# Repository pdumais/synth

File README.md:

# Modular Synthesizer

# Design
- 5V system, but requires +12,-12 rails for modules using opamps
- uses computer PSU
- 2 signal paths:
    1) The audio signal. -5 - +5V. 
    2) Control Voltages. They work on unipolar 5V.

# Current modules
- [dual VCO and quad LFO. Square only](modules/osc)
- [LFO shaper: to convert square to trianble/sine or anything in between](modules/waveshaper)
- [Sequencer](modules/sequencer)
- [Clock](modules/clock)
- [Clock Divider](modules/divider)
- [Voltage Controlled Resistors](modules/digipot)
- [Midi2CV](modules/midi2cv)
- [Noise Generator](modules/noise)
- [4 Channel VCA](modules/vca)
- [4 stage VCF](modules/vcf)

# Known issues
- Power filtering
    The oscilloscope shows that the -5 and +5 rails oscillate at an amplitude of 0.4v. The wave has a period of 500ns.
    That's 2mhz. 
    For the CV path, this gets filtered out by the sampling rate of the ADC, so no need to do anything about it. When CV
    is used with analog, it wouldn't be audible anyway.

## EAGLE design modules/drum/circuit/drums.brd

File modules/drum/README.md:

Bass drum demo: https://www.youtube.com/watch?v=A4alrGFjpv0

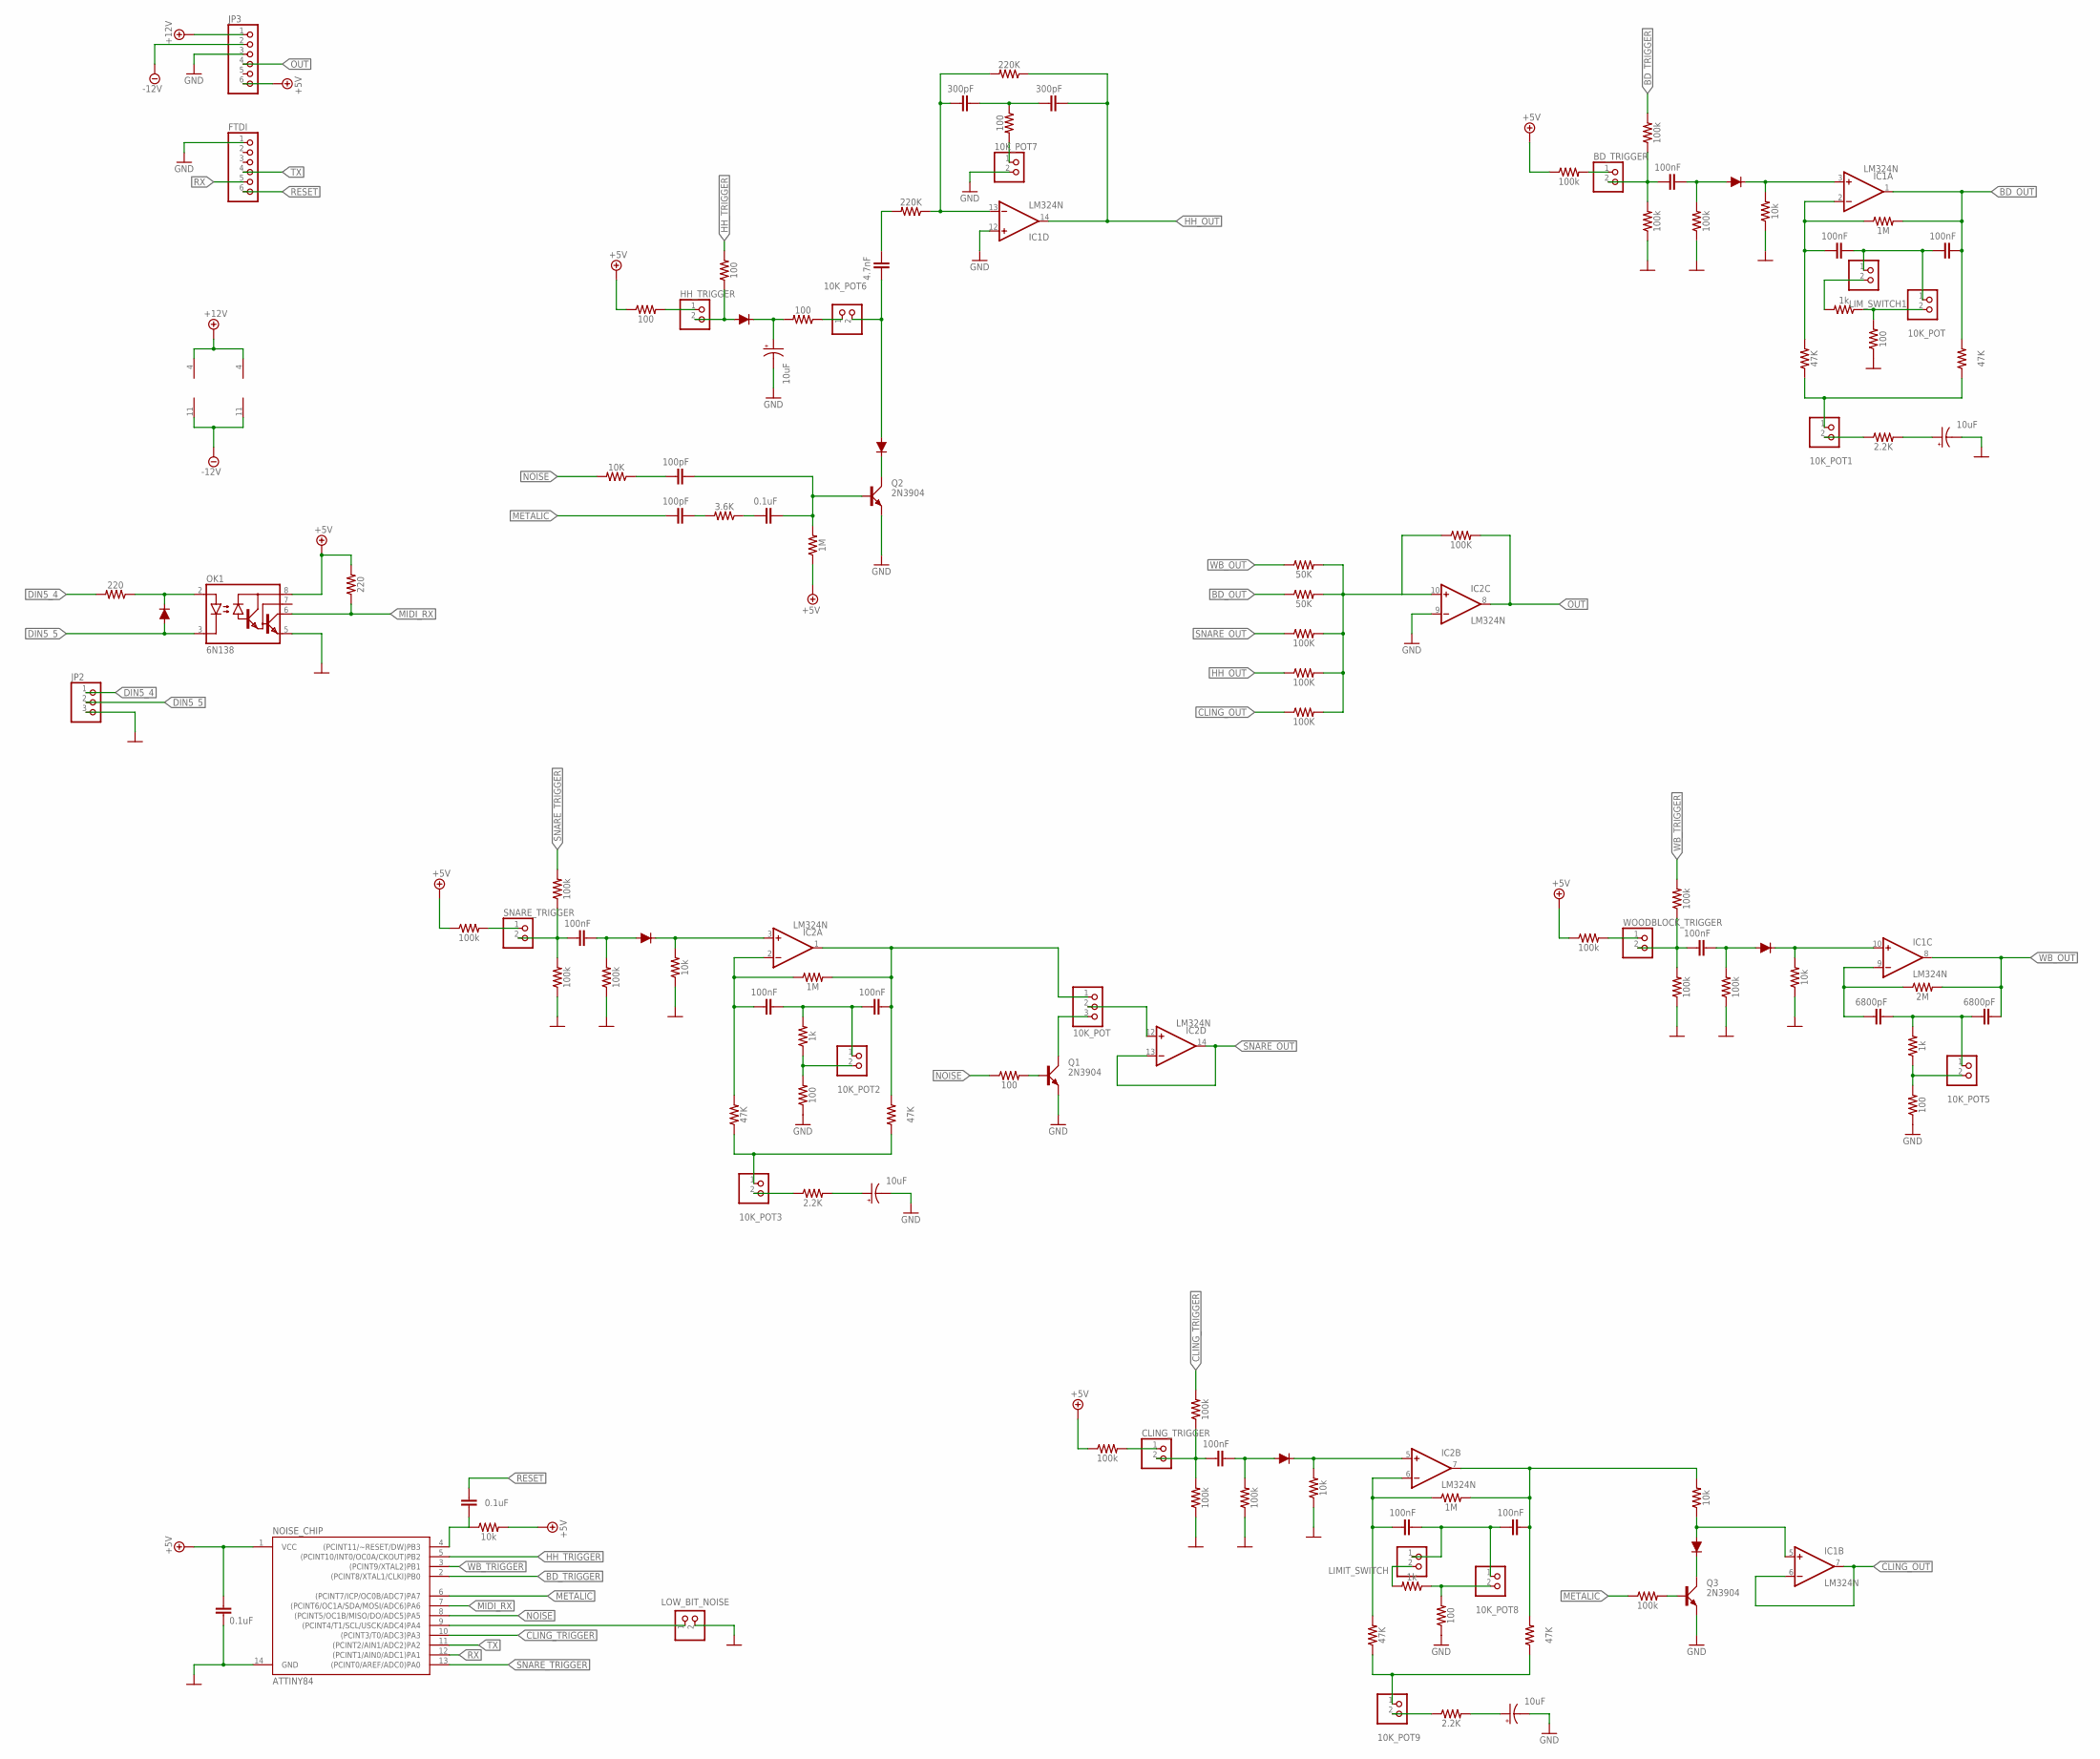
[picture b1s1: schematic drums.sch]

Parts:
1M: 1M; AXIAL-0.3
1M1, 1M2: 220; AXIAL-0.3
10K_POT, 10K_POT1, 10K_POT2, 10K_POT3, 10K_POT5, 10K_POT6, 10K_POT7, 10K_POT8, 10K_POT9: PINHD-1X2; 1X02
10K_POT4: 10K_POT; 1X03
BD_TRIGGER: PINHD-1X2; 1X02
C1, C4, C12: 0.1uF; C5B3
C2, C3, C6, C7, C18, C19, C20, C21, C22, C24: 100nF; C5B3
C5, C8, C11, C23: 10uF; TT5D11
C9, C10: 6800pF; C5B3
C13, C14: 100pF; C5B3
C15: 4.7nF; C5B3
C16, C17: 300pF; C5B3
CLING_TRIGGER: PINHD-1X2; 1X02
D1, D2, D3, D4, D5, D6, D7, D8: 1A/50V/1.1V; DIODE-1N4001-KIT
FTDI: PINHD-1X6; 1X06
HH_TRIGGER: PINHD-1X2; 1X02
IC1, IC2: LM324N; DIL14
JP2: PINHD-1X3; 1X03
JP3: PINHD-1X6; 1X06
LIMIT_SWITCH: PINHD-1X2; 1X02
LIM_SWITCH1: PINHD-1X2; 1X02
LOW_BIT_NOISE: PINHD-1X2; 1X02
NOISE_CHIP: ATTINY84; DIP14
OK1: 6N138; DIL08
Q1, Q2, Q3: 2N3904; TO92D
R1, R12, R19, R20, R23, R38, R39, R41, R42, R43, R44, R45, R52, R54, R55, R56, R57: 100k; AXIAL-0.3
R2, R22, R25, R40, R53, R59: 10k; AXIAL-0.3
R3, R13, R46: 1M; AXIAL-0.3
R4, R5, R14, R15, R47, R48: 47K; AXIAL-0.3
R6, R16, R27, R49: 1k; AXIAL-0.3
R7, R11, R17, R21, R26, R28, R29, R36, R50: 100; AXIAL-0.3
R8, R18, R51: 2.2K; AXIAL-0.3
R9, R31: 50K; AXIAL-0.3
R10, R30, R37, R58: 100K; AXIAL-0.3
R24: 2M; AXIAL-0.3
R32: 3.6K; AXIAL-0.3
R33: 10K; AXIAL-0.3
R34, R35: 220K; AXIAL-0.3
SNARE_TRIGGER: PINHD-1X2; 1X02
WOODBLOCK_TRIGGER: PINHD-1X2; 1X02

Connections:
10K_POT1: 10K_POT1.1, R4.P$1 (1), R5.P$1 (1)
10K_POT2: 10K_POT3.1, R14.P$1 (1), R15.P$1 (1)
10K_POT3: 10K_POT9.1, R47.P$1 (1), R48.P$1 (1)
+5V: 1M.P$1 (1), 1M1.P$2 (2), C1.1, JP3.6, NOISE_CHIP.1 (VCC), OK1.8 (VCC), R23.P$1 (1), R25.P$2 (2), R29.P$1 (1), R38.P$1 (1), R41.P$1 (1), R54.P$1 (1)
+12V: IC1.4 (V+), IC2.4 (V+), JP3.1
-12V: IC1.11 (V-), IC2.11 (V-), JP3.2
BD_OUT: 10K_POT4.1, C3.2, C7.2, IC1.1 (OUT), IC2.1 (OUT), R3.P$2 (2), R5.P$2 (2), R13.P$2 (2), R15.P$2 (2), R31.P$1 (1)
BD_OUT1: C22.2, IC2.7 (OUT), R46.P$2 (2), R48.P$2 (2), R59.P$2 (2)
BD_TRIGGER: NOISE_CHIP.2 ((PCINT8/XTAL1/CLKI)PB0), R12.P$2 (2)
CLING_OUT: IC1.6 (-IN), IC1.7 (OUT), R58.P$1 (1)
CLING_TRIGGER: NOISE_CHIP.10 ((PCINT3/T0/ADC3)PA3), R57.P$2 (2)
DIN5_4: 1M2.P$2 (2), JP2.1
DIN5_5: D2.A, JP2.2, OK1.3 (C)
GND: 10K_POT7.2, C1.2, C5.-, C8.-, C11.-, C23.-, FTDI.1, IC1.12 (+IN), IC2.9 (-IN), JP2.3, JP3.3, LOW_BIT_NOISE.2, NOISE_CHIP.14 (GND), OK1.5 (GND), Q1.E, Q2.E, Q3.E, R1.P$1 (1), R2.P$1 (1), R7.P$1 (1), R17.P$1 (1), R22.P$1 (1), R28.P$1 (1), R39.P$1 (1), R40.P$1 (1), R42.P$1 (1), R43.P$1 (1), R44.P$1 (1), R45.P$1 (1), R50.P$1 (1), R53.P$1 (1), R55.P$1 (1), R56.P$1 (1)
HH_OUT: C17.2, IC1.14 (OUT), R35.P$1 (1), R37.P$1 (1)
HH_TRIGGER: NOISE_CHIP.5 ((PCINT10/INT0/OC0A/CKOUT)PB2), R11.P$2 (2)
METALIC: C14.1, NOISE_CHIP.6 ((PCINT7/ICP/OC0B/ADC7)PA7), R52.P$1 (1)
MIDI_RX: 1M1.P$1 (1), NOISE_CHIP.7 ((PCINT6/OC1A/SDA/MOSI/ADC6)PA6), OK1.6 (VO)
unnamed: 10K_POT8.1, C21.2, C22.1, LIMIT_SWITCH.1
unnamed: BD_TRIGGER.2, C18.1, R12.P$1 (1), R39.P$2 (2)
unnamed: D1.C, IC1.3 (+IN), R2.P$2 (2)
unnamed: C18.2, D1.A, R1.P$2 (2)
unnamed: BD_TRIGGER.1, R38.P$2 (2)
unnamed: 10K_POT.1, C2.2, C3.1, LIM_SWITCH1.1
unnamed: C2.1, IC1.2 (-IN), R3.P$1 (1), R4.P$2 (2)
unnamed: C21.1, IC2.6 (-IN), R46.P$1 (1), R47.P$2 (2)
unnamed: 10K_POT.2, R6.P$1 (1), R7.P$2 (2)
unnamed: 10K_POT1.2, R8.P$1 (1)
unnamed: C5.+, R8.P$2 (2)
unnamed: 1M2.P$1 (1), D2.C, OK1.2 (A)
unnamed: 10K_POT8.2, R49.P$1 (1), R50.P$2 (2)
unnamed: 10K_POT9.2, R51.P$1 (1)
unnamed: C19.1, R19.P$1 (1), R42.P$2 (2), WOODBLOCK_TRIGGER.2
unnamed: 10K_POT2.1, C6.2, C7.1, R16.P$2 (2)
unnamed: C6.1, IC2.2 (-IN), R13.P$1 (1), R14.P$2 (2)
unnamed: 10K_POT2.2, R16.P$1 (1), R17.P$2 (2)
unnamed: 10K_POT3.2, R18.P$1 (1)
unnamed: C8.+, R18.P$2 (2)
unnamed: C23.+, R51.P$2 (2)
unnamed: Q1.B, R21.P$2 (2)
unnamed: 10K_POT4.3, Q1.C
unnamed: 10K_POT4.2, IC2.12 (+IN)
unnamed: C20.1, R20.P$1 (1), R44.P$2 (2), SNARE_TRIGGER.2
unnamed: D3.C, IC2.3 (+IN), R22.P$2 (2)
unnamed: R23.P$2 (2), SNARE_TRIGGER.1
unnamed: D6.C, IC1.10 (+IN), R40.P$2 (2)
unnamed: 10K_POT5.1, C9.2, C10.1, R27.P$2 (2)
unnamed: C9.1, IC1.9 (-IN), R24.P$1 (1)
unnamed: 10K_POT5.2, R27.P$1 (1), R28.P$2 (2)
unnamed: D4.A, HH_TRIGGER.2, R11.P$1 (1)
unnamed: C11.+, D4.C, R26.P$2 (2)
unnamed: IC2.10 (+IN), R9.P$2 (2), R10.P$2 (2), R30.P$1 (1), R31.P$2 (2), R37.P$2 (2), R58.P$2 (2)
unnamed: 10K_POT6.1, R26.P$1 (1)
unnamed: 10K_POT6.2, C15.1, D5.A
unnamed: C4.2, NOISE_CHIP.4 ((PCINT11/~RESET/DW)PB3), R25.P$1 (1)
unnamed: D5.C, Q2.C
unnamed: C12.1, R32.P$1 (1)
unnamed: 1M.P$2 (2), C12.2, C13.2, Q2.B
unnamed: HH_TRIGGER.1, R29.P$2 (2)
unnamed: C13.1, R33.P$1 (1)
unnamed: C15.2, R34.P$2 (2)
unnamed: C14.2, R32.P$2 (2)
unnamed: 10K_POT7.1, R36.P$2 (2)
unnamed: C16.2, C17.1, R36.P$1 (1)
unnamed: R41.P$2 (2), WOODBLOCK_TRIGGER.1
unnamed: C16.1, IC1.13 (-IN), R34.P$1 (1), R35.P$2 (2)
unnamed: C19.2, D6.A, R43.P$2 (2)
unnamed: C20.2, D3.A, R45.P$2 (2)
unnamed: Q3.B, R52.P$2 (2)
unnamed: D8.C, Q3.C
unnamed: D8.A, IC1.5 (+IN), R59.P$1 (1)
unnamed: C24.1, CLING_TRIGGER.2, R55.P$2 (2), R57.P$1 (1)
unnamed: D7.C, IC2.5 (+IN), R53.P$2 (2)
unnamed: CLING_TRIGGER.1, R54.P$2 (2)
unnamed: C24.2, D7.A, R56.P$2 (2)
unnamed: LIM_SWITCH1.2, R6.P$2 (2)
unnamed: LIMIT_SWITCH.2, R49.P$2 (2)
unnamed: LOW_BIT_NOISE.1, NOISE_CHIP.9 ((PCINT4/T1/SCL/USCK/ADC4)PA4)
NOISE: NOISE_CHIP.8 ((PCINT5/OC1B/MISO/DO/ADC5)PA5), R21.P$1 (1), R33.P$2 (2)
OUT: IC2.8 (OUT), JP3.4, R30.P$2 (2)
RESET: C4.1, FTDI.6
RX: FTDI.5, NOISE_CHIP.12 ((PCINT1/AIN0/ADC1)PA1)
SNARE_OUT: IC2.13 (-IN), IC2.14 (OUT), R10.P$1 (1)
SNARE_TRIGGER: NOISE_CHIP.13 ((PCINT0/AREF/ADC0)PA0), R20.P$2 (2)
TX: FTDI.4, NOISE_CHIP.11 ((PCINT2/AIN1/ADC2)PA2)
WB_OUT: C10.2, IC1.8 (OUT), R9.P$1 (1), R24.P$2 (2)
WB_TRIGGER: NOISE_CHIP.3 ((PCINT9/XTAL2)PB1), R19.P$2 (2)

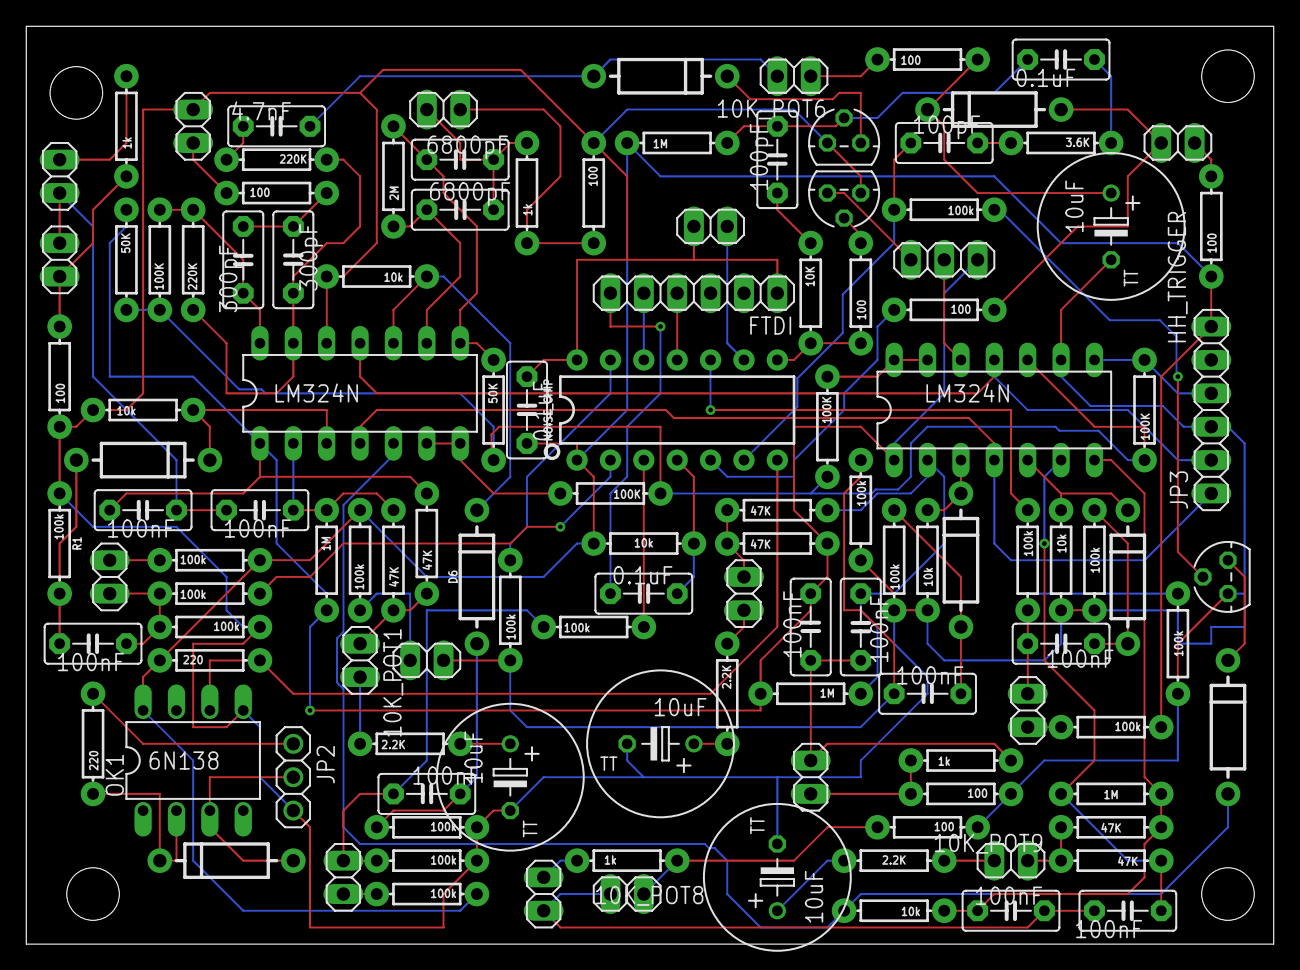
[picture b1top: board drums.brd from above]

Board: 2 copper layers, 94.9 x 69.8 mm, 122 parts (0 on the bottom side), 87 nets.

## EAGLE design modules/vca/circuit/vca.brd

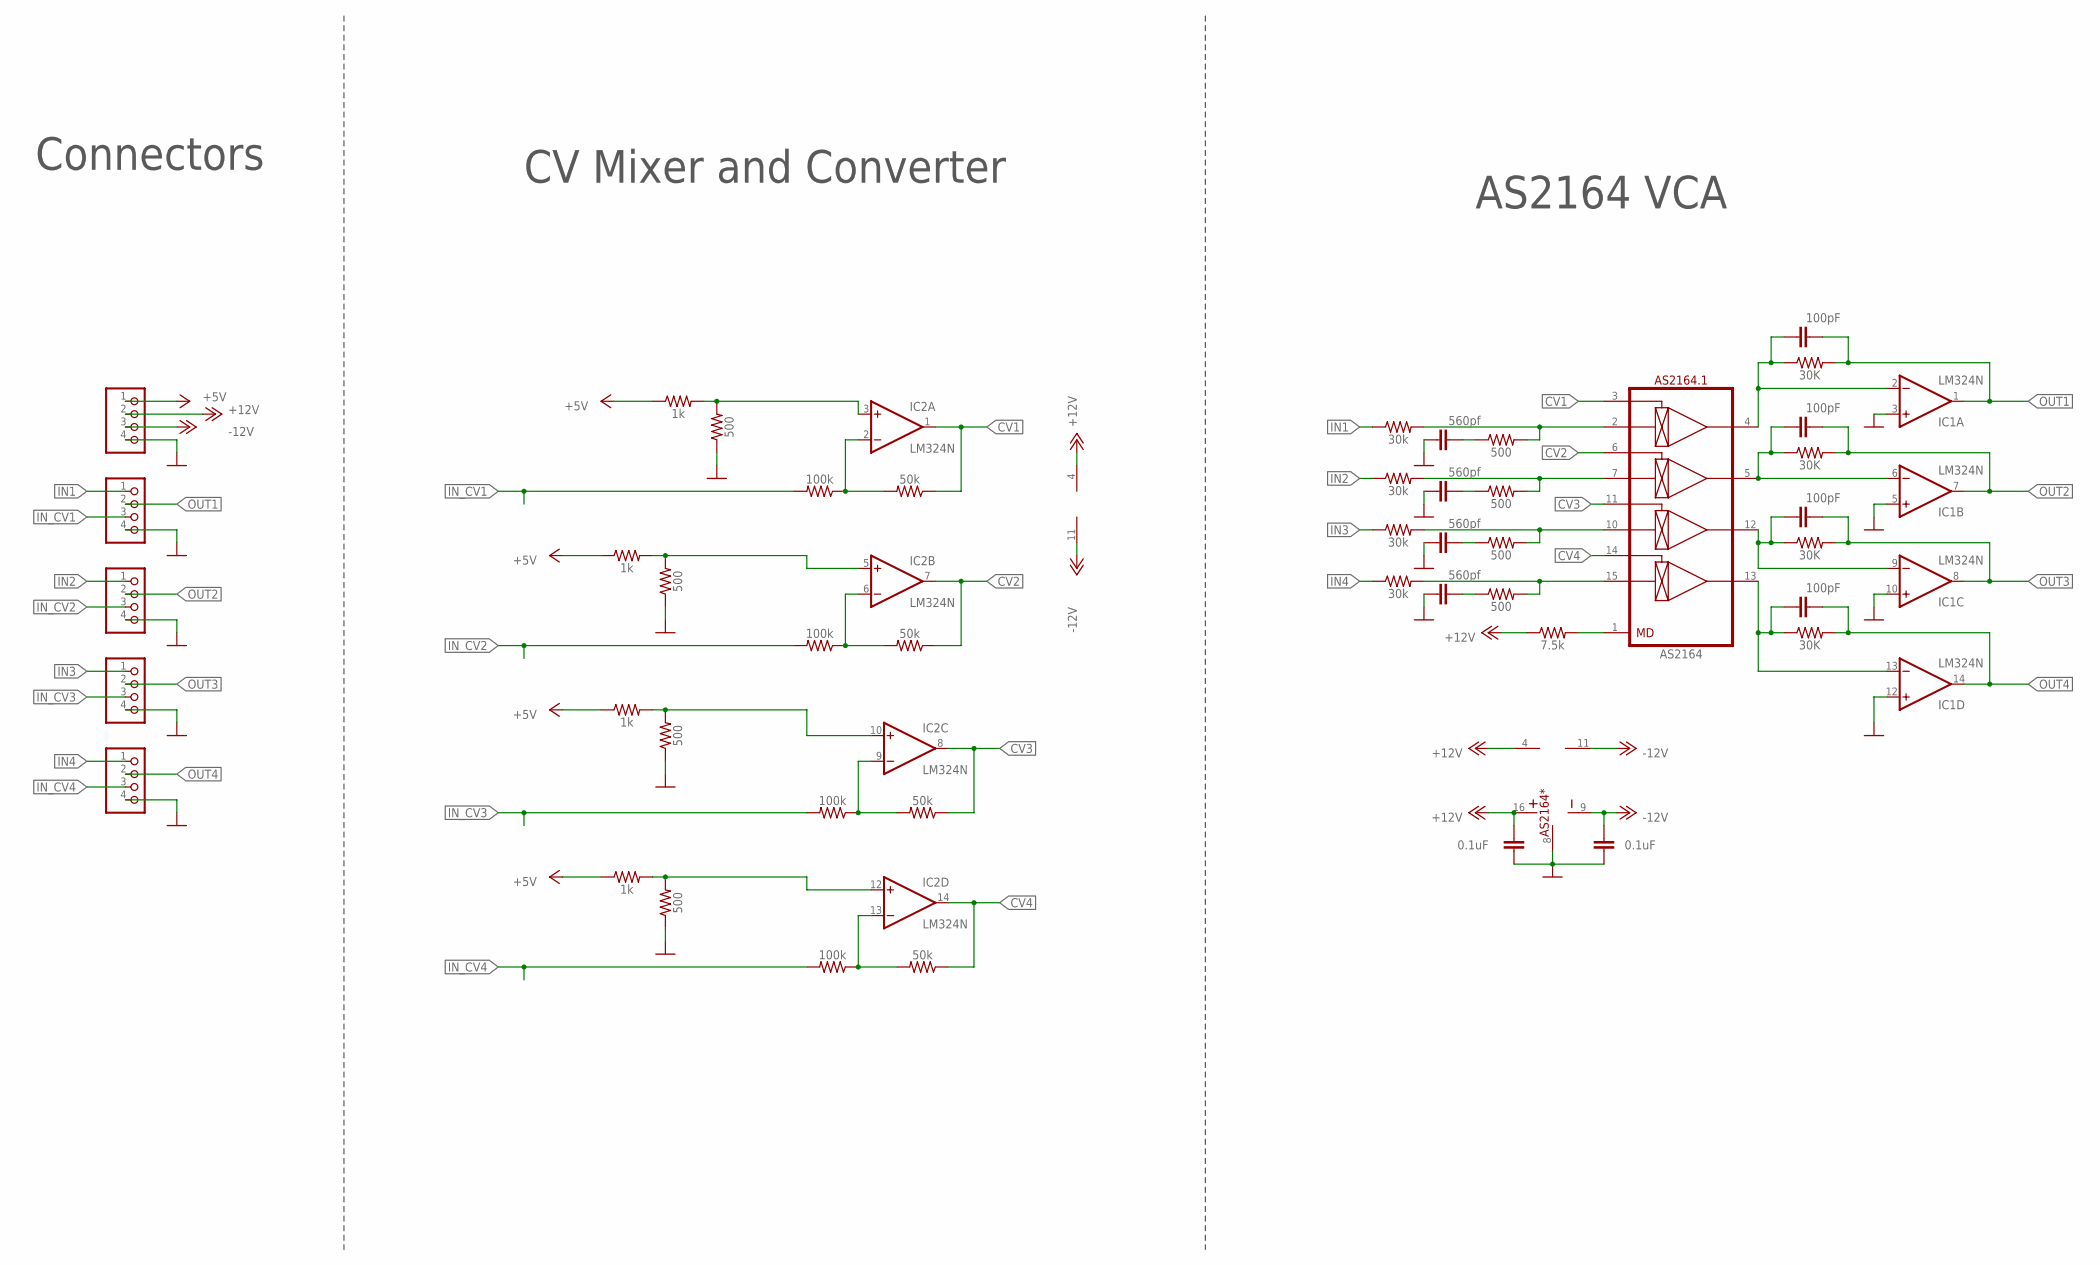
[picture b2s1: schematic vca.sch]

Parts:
AS2164: AS2164; DIP-16
C1, C2, C3, C4: 560pf; CAP-PTH-SMALL-KIT
C5, C6: 0.1uF; CAP-PTH-SMALL-KIT
C7, C8, C9, C10: 100pF; CAP-PTH-SMALL-KIT
IC1, IC2: LM324N; DIL14
JP1, JP5, JP6, JP7, JP8: PINHD-1X4; 1X04
R1, R2, R3, R5: 30k; AXIAL-0.3
R4, R6, R7, R8, R9, R14, R18, R22: 500; AXIAL-0.3
R10, R13, R17, R21: 1k; AXIAL-0.3
R11, R15, R19, R23: 100k; AXIAL-0.3
R12, R16, R20, R24: 50k; AXIAL-0.3
R25: 7.5k; AXIAL-0.3
R26, R27, R28, R29: 30K; AXIAL-0.3

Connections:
+5V: JP6.1, R10.P$1 (1), R13.P$1 (1), R17.P$1 (1), R21.P$1 (1)
+12V: AS2164.16 (V+), C5.2, IC1.4 (V+), IC2.4 (V+), JP6.2, R25.P$1 (1)
-12V: AS2164.9 (V-), C6.2, IC1.11 (V-), IC2.11 (V-), JP6.3
CV1: AS2164.3 (CV1), IC2.1 (OUT), R20.P$1 (1)
CV2: AS2164.6 (CV2), IC2.7 (OUT), R16.P$1 (1)
CV3: AS2164.11 (CV3), IC2.8 (OUT), R12.P$1 (1)
CV4: AS2164.14 (CV4), IC2.14 (OUT), R24.P$1 (1)
GND: AS2164.8 (GND), C1.1, C2.1, C3.1, C4.1, C5.1, C6.1, IC1.3 (+IN), IC1.5 (+IN), IC1.10 (+IN), IC1.12 (+IN), JP1.4, JP5.4, JP6.4, JP7.4, JP8.4, R9.P$1 (1), R14.P$1 (1), R18.P$1 (1), R22.P$1 (1)
IN1: JP5.1, R1.P$1 (1)
IN2: JP7.1, R2.P$1 (1)
IN3: JP1.1, R3.P$1 (1)
IN4: JP8.1, R5.P$1 (1)
IN_CV1: JP5.3, R19.P$2 (2)
IN_CV2: JP7.3, R15.P$2 (2)
IN_CV3: JP1.3, R11.P$2 (2)
IN_CV4: JP8.3, R23.P$2 (2)
unnamed: AS2164.2 (IN1), R1.P$2 (2), R8.P$2 (2)
unnamed: AS2164.7 (IN2), R2.P$2 (2), R7.P$2 (2)
unnamed: AS2164.10 (IN3), R3.P$2 (2), R6.P$2 (2)
unnamed: AS2164.15 (IN4), R4.P$2 (2), R5.P$2 (2)
unnamed: C1.2, R8.P$1 (1)
unnamed: C2.2, R7.P$1 (1)
unnamed: C3.2, R6.P$1 (1)
unnamed: C4.2, R4.P$1 (1)
unnamed: IC2.5 (+IN), R13.P$2 (2), R14.P$2 (2)
unnamed: IC2.3 (+IN), R9.P$2 (2), R10.P$2 (2)
unnamed: IC2.9 (-IN), R11.P$1 (1), R12.P$2 (2)
unnamed: IC2.10 (+IN), R17.P$2 (2), R18.P$2 (2)
unnamed: IC2.12 (+IN), R21.P$2 (2), R22.P$2 (2)
unnamed: IC2.6 (-IN), R15.P$1 (1), R16.P$2 (2)
unnamed: IC2.2 (-IN), R19.P$1 (1), R20.P$2 (2)
unnamed: IC2.13 (-IN), R23.P$1 (1), R24.P$2 (2)
unnamed: AS2164.1 (MD), R25.P$2 (2)
unnamed: AS2164.13 (OUT4), C7.1, IC1.13 (-IN), R26.P$1 (1)
unnamed: AS2164.12 (OUT3), C8.1, IC1.9 (-IN), R27.P$1 (1)
unnamed: AS2164.5 (OUT2), C9.1, IC1.6 (-IN), R28.P$1 (1)
unnamed: AS2164.4 (OUT1), C10.1, IC1.2 (-IN), R29.P$1 (1)
OUT1: C10.2, IC1.1 (OUT), JP5.2, R29.P$2 (2)
OUT2: C9.2, IC1.7 (OUT), JP7.2, R28.P$2 (2)
OUT3: C8.2, IC1.8 (OUT), JP1.2, R27.P$2 (2)
OUT4: C7.2, IC1.14 (OUT), JP8.2, R26.P$2 (2)

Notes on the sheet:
Connectors
CV Mixer and Converter
AS2164 VCA

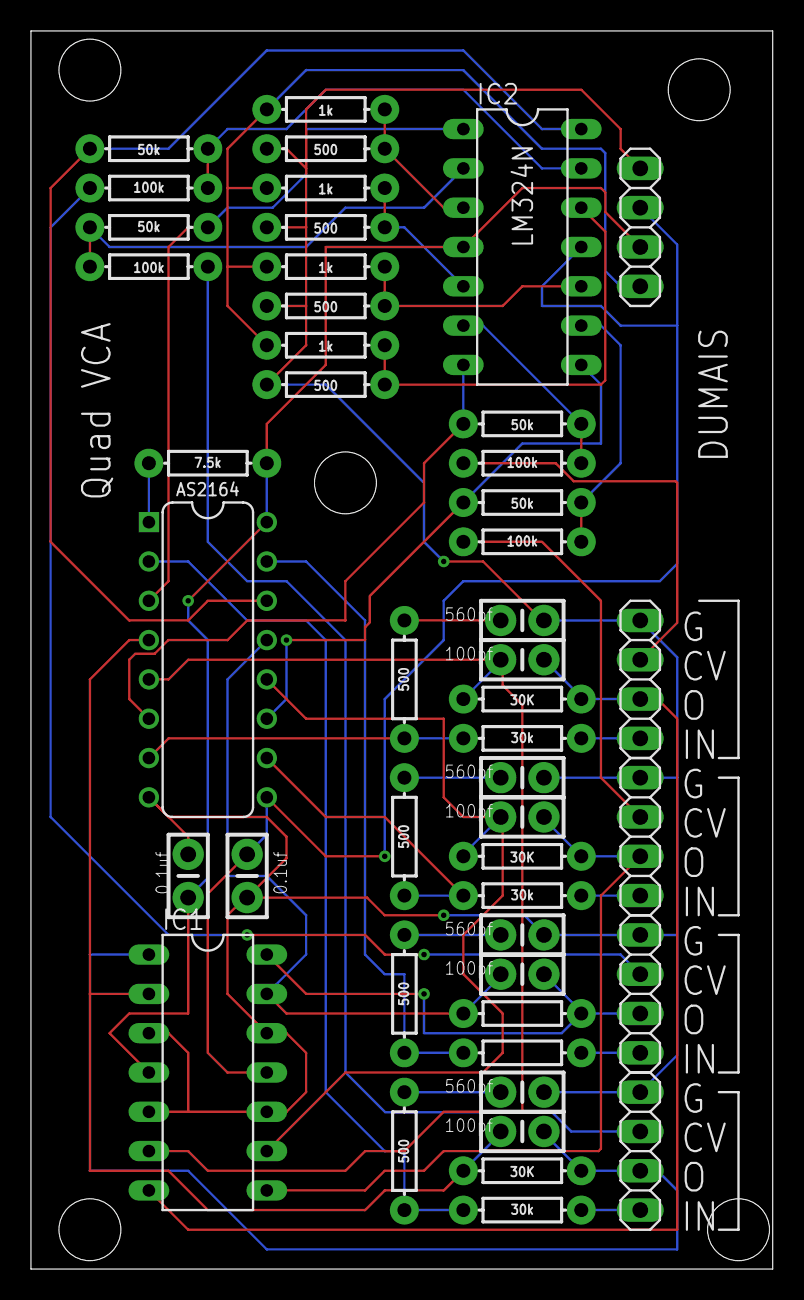
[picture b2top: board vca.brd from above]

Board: 2 copper layers, 47.9 x 80.0 mm, 47 parts (0 on the bottom side), 41 nets.

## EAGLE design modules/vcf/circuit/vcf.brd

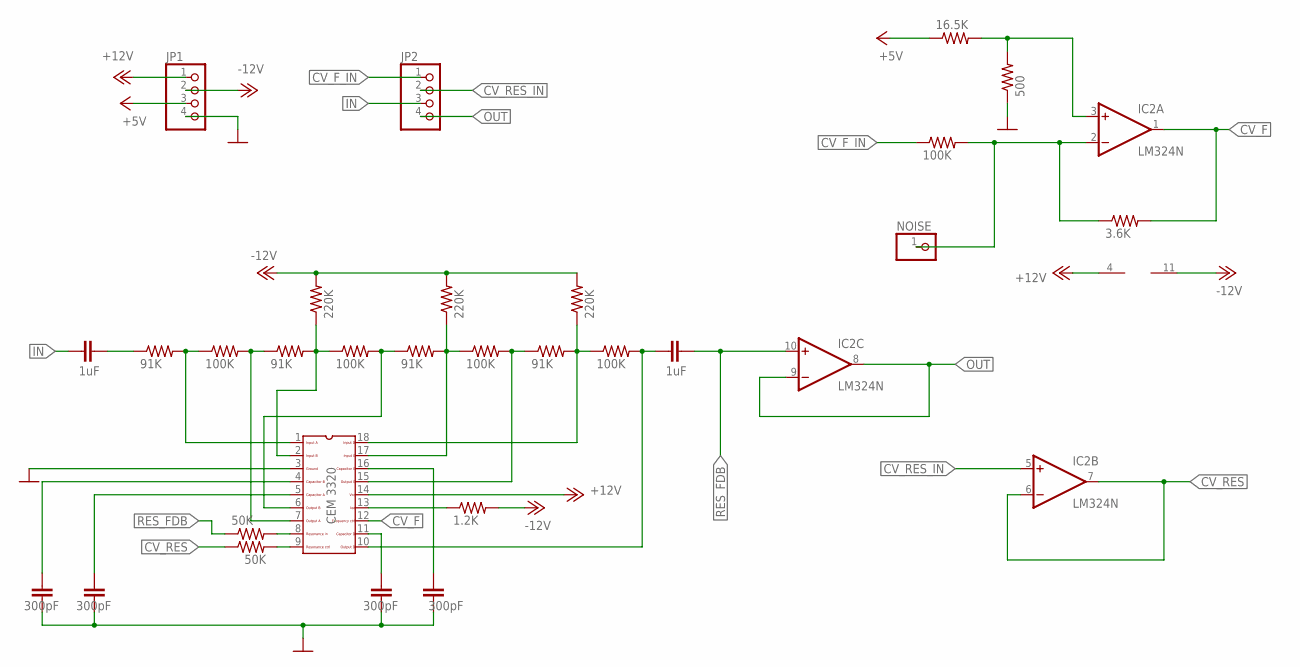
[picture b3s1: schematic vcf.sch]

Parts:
C1, C2, C3, C4: 300pF; C025-030X050
C5, C6: 1uF; C025-030X050
IC1: CEM3320; DIL18
IC2: LM324N; DIL14
JP1, JP2: PINHD-1X4; 1X04
NOISE: PINHD-1X1; 1X01
R1: 1.2K; 0204/7
R2, R4, R6, R8: 91K; 0204/7
R3, R5, R7, R9, R15: 100K; 0204/7
R10, R11, R12: 220K; 0204/7
R13: 16.5K; 0204/7
R14: 500; 0204/7
R16: 3.6K; 0204/7
R17, R18: 50K; 0204/7

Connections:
+5V: JP1.3, R13.1
+12V: IC1.14, IC2.4 (V+), JP1.1
-12V: IC2.11 (V-), JP1.2, R1.2, R10.2, R11.2, R12.2
CV_F: IC1.12, IC2.1 (OUT), R16.2
CV_F_IN: JP2.1, R15.1
CV_RES: IC2.6 (-IN), IC2.7 (OUT), R18.1
CV_RES_IN: IC2.5 (+IN), JP2.2
GND: C1.2, C2.2, C3.2, C4.2, IC1.3, JP1.4, R14.1
IN: C6.1, JP2.3
unnamed: IC1.13, R1.1
unnamed: C4.1, IC1.4
unnamed: C3.1, IC1.5
unnamed: C1.1, IC1.11
unnamed: C2.1, IC1.16
unnamed: IC1.1, R2.2, R3.1
unnamed: IC1.7, R3.2, R4.1
unnamed: IC1.2, R4.2, R5.1, R11.1
unnamed: IC1.6, R5.2, R6.1
unnamed: IC1.17, R6.2, R7.1, R10.1
unnamed: IC1.15, R7.2, R8.1
unnamed: IC1.18, R8.2, R9.1, R12.1
unnamed: IC2.3 (+IN), R13.2, R14.2
unnamed: C5.1, IC1.10, R9.2
unnamed: IC2.2 (-IN), NOISE.1, R15.2, R16.1
unnamed: C6.2, R2.1
unnamed: IC1.8, R17.2
unnamed: IC1.9, R18.2
OUT: IC2.8 (OUT), IC2.9 (-IN), JP2.4
RES_FDB: C5.2, IC2.10 (+IN), R17.1

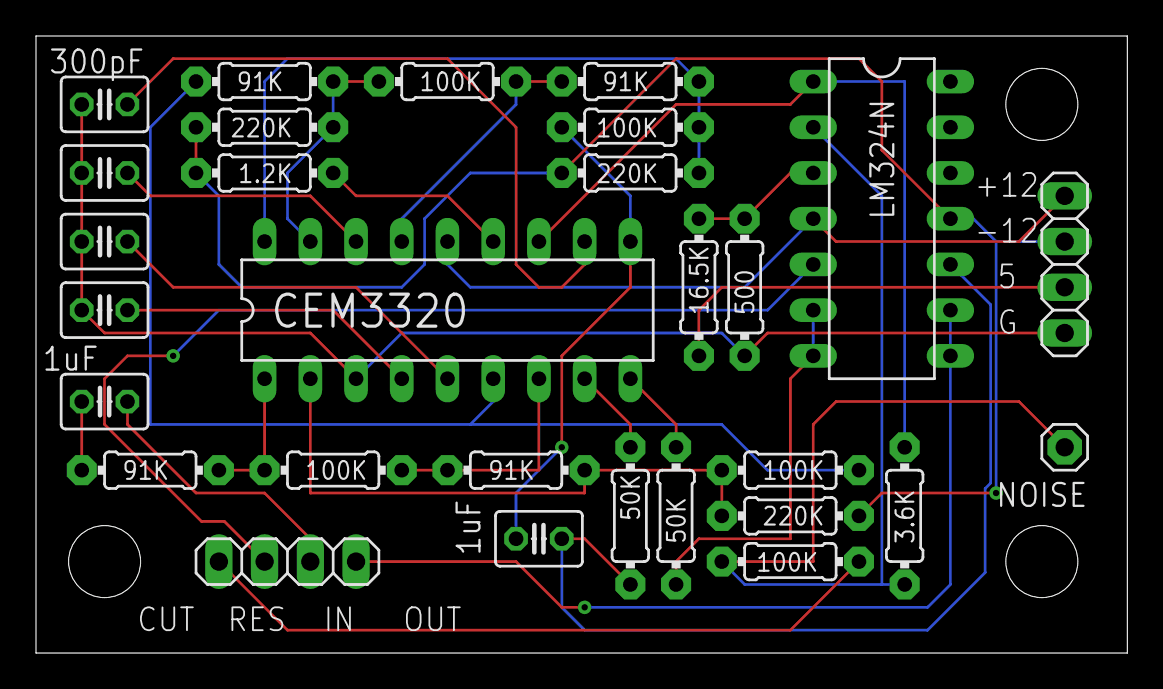
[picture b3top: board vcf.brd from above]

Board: 2 copper layers, 60.6 x 34.3 mm, 29 parts (0 on the bottom side), 29 nets.

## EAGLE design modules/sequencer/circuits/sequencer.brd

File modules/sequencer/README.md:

# UPDATE
This turns out to be a not so good design.
The stepper and the binary counter are out of sink, so the step number being displayed is not accurate. I suspect
that this is happening because of a difference in startup time betewen both chips, so one chip misses
a clock while the other has processed one already.

But the sequencing part of it does work. So It's a good prototype.

# Design
This is a 8 step sequencer based on the 4017 counter. 

The 4017's Q1 to Q8 outputs go through 8 optentiometers which are all connected to unity gain opamp. The opamp is used to limit the current draw from the system after going out on the CV output

I had a lot of help from this thread: https://www.modwiggler.com/forum/viewtopic.php?t=258437
I'm not sure why having all pots connected together with a 100K resistor doesn't create a voltage divider. It used to create
on and it was a problem. But by connecting everything the the inverting amplifier at the end, it solved that problem. 
At the time of writing this, I don't understand why.

What I didn't like about popular designs that I saw, was that they were all using diodes. The voltage drop of the diode would 
affect the CV by a great margin IMO. With my design, I don't get any voltage drops so CV should be quite accurate. 

## Keeping it simple
As I was designing this module, I realized how many more features I could add to it but it would become increasingly difficult and
more expensive to do so. I realized that I would be much better off to build it with a microcontroller instead. But I decided
to keep using the 4017 because it was an interesting design. 
These are the things I would've liked to do, but decided to hold off until I build a full digital sequencer. The following list 
is more like personal notes so that I can remember later why I didn't implement those.
- A pause button: This sounds simple because all I have to do is inhibit the clock on the 4017 and on the 4163. But both chips
  expect a high and low signal respectively. So I would need a NOT gate for one of them. But then I also need to inhibit the clock
  out of the gate and actually keep that signal high. Instead of using a NOT gate on one of the ic, I could simply cut the clock source.
  but then I would need to tie both ic's clk pins to ground. If I leave it high, I risk creating a rising edge so the pause would 
  force a move to the next step and then pause. So I need to ground the clock signal for the whole circuit, but raise the gate signal.
  it's getting a bit complicated
- Randomizer:To be able to randomly shuffle steps. That's just not something you can do with the 4017.
- variable step length: it would be possible to create the circuitry to manipulate the clock entering the 4017 and multiply/divide 
  for every step. But that's a lot more components to add and becomes more expensive. This is something that is just easier with a 
  microcontroller

## 74163 binary counter
NOTE: This is no longer in the design. Because the 74163 starts with all outputs high and goes to 0 after the first clock
      That's out of sync with the 4017. So I removed that. It could've worked with the 74161 maybe.

The 74163 (4 bit binary counter) is used to control the daisy chaining. QD will be low for the first 8 clocks and then high 
for the next 8 clocks. This is used to control which of the 2 sequencers are active when daisy chained. there are 6 pins that 
require a jumper to control the daisy-chain operation 
    - A jumper between pin 1&2 will make the 4017 active  (by controlling the vcc line) when 4163.QD is high, 
      so during steps 9-16. This is the setting required for the second sequencer
    - A jumper between pin 3&4 will make the 4017 active  (by controlling the vcc line) when 4163.QD is 
      low, so during steps 1-8. This is the setting required for the first sequencer
    - A jumper between pin 5&6 will make the 4017 active  (by controlling the vcc line) all the time, 
      bypassing the 4163 logic. This is the setting required when running a standalone sequencer (8 steps only)
 
Note that both sequencers run their own 4163, so it is possible to configure them in a conflicting manner.

When daisy-chaining, a cable needs to be connected between both sequencers so that:
    - the reset line is connected between both sequencers so that pressing the reset button will act on both sequencers
    - the enable line is connected between both sequencers so that pressing the start/stop button will act on both sequencers

## Gate
The gate signal is fed to a monostable multivibrator that generates a gate signal at the same frequency than the input clock. The pulse width cn be adjusted
beteen 160ms to 1.8s through a 10k potentionmeter

## Inputs / Outputs
### Inputs
    - Clock in
    - Buttons to shorten the sequence to 2 or 4 steps. 
    - Power: +12, -12, +5, Ground 
    - 8 pins for potentiometers wipers, 8 pins for their input voltage from the 4017, 1 pin for their ground
### Outputs
    - CV
    - Gate

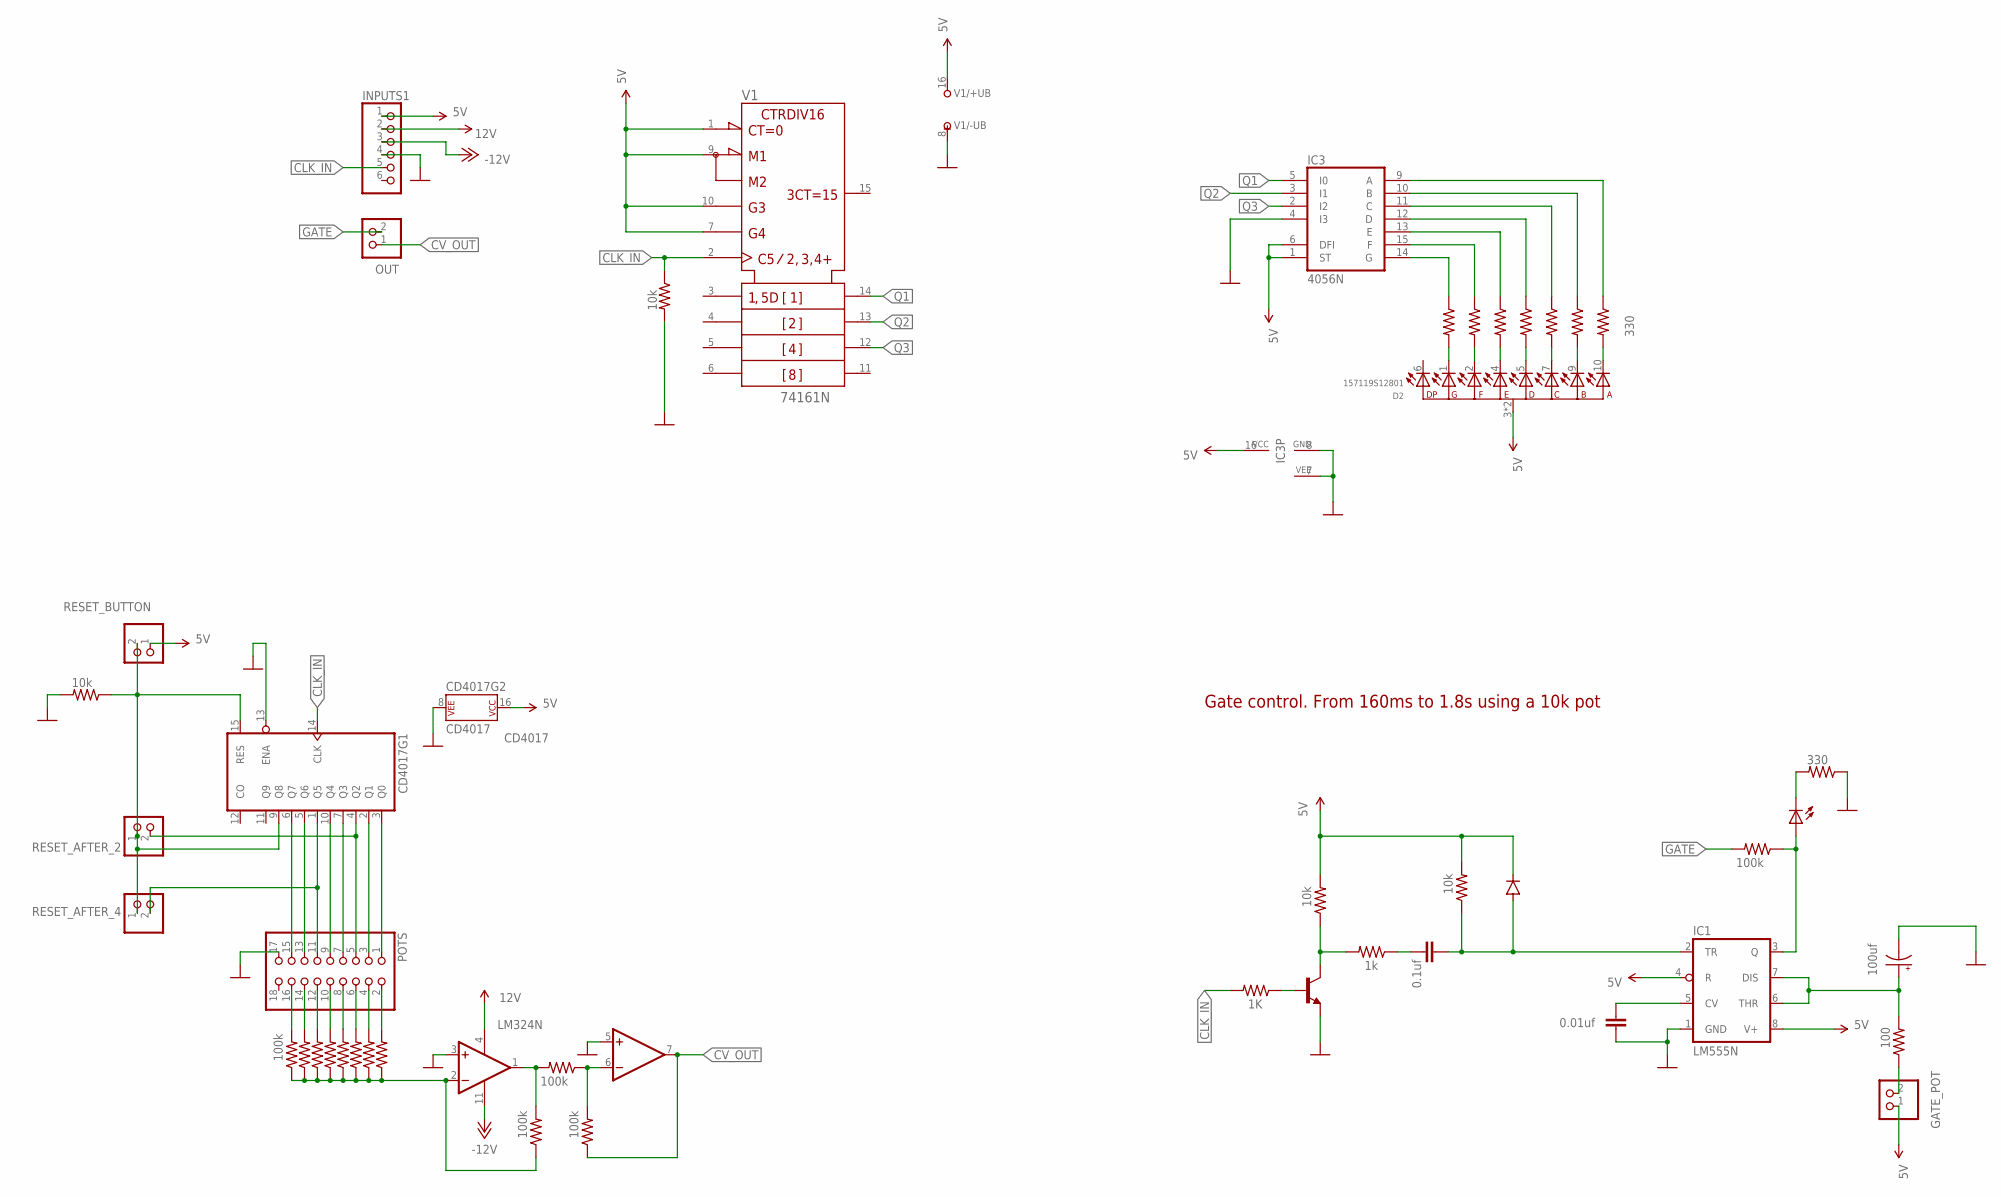
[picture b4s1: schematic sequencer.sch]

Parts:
1K1: 100k; 0207/12
1K3: 1k; 0207/12
1K4: 10k; 0207/12
2N2: 2N4401-NPN-TO92-EBC; TO92-EBC
C1: 0.01uf; C025-024X044
C3: 100uf; E2,5-6E
C4: 0.1uf; C025-024X044
CD4017: CD4017; DIP16
D1: 1N4004; DO41-10
D2: 157119S12801; WL-T7DS_0.39INCH
GATE_POT: PINHD-1X2; 1X02
IC1: LM555N; DIL08-ROUND
IC2: LM324N; DIL14
IC3: 4056N; DIL16
INPUTS1: PINHD-1X6; 1X06
LED9: LED5MM
OUT: PINHD-1X2; 1X02
POTS: PINHD-2X9; 2X09
R1, R13, R14, R15, R16, R17, R18, R23: 330; 0207/12
R2, R3, R4, R5, R6, R7, R8, R9, R10, R11, R12: 100k; 0207/12
R19: 1K; 0207/12
R20, R22, R24: 10k; 0207/12
R21: 100; 0207/12
RESET_AFTER_2, RESET_AFTER_4: PINHD-1X2; 1X02
RESET_BUTTON: PINHD-1X2; 1X02
V1: 74161N; DIL16

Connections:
5V: 1K4.2, CD4017.16 (P$V+), D1.C, D2.3 (+), D2.8 (+), GATE_POT.1, IC1.4 (R), IC1.8 (V+), IC3.1 (ST), IC3.6 (DFI), IC3.16 (VCC), INPUTS1.1, R20.2, RESET_BUTTON.1, V1.1 (!CLR), V1.7 (ENP), V1.9 (!LOAD), V1.10 (ENT), V1.16 (+UB)
12V: IC2.4 (V+), INPUTS1.2
-12V: IC2.11 (V-), INPUTS1.3
CLK_IN: CD4017.14 (CLK), INPUTS1.5, R19.2, R24.1, V1.2 (CLK)
CV_OUT: IC2.7 (OUT), OUT.1, R11.1
GATE: 1K1.2, OUT.2
GND: 2N2.E, C1.2, C3.-, CD4017.8 (P$V-), CD4017.13 (ENA), IC1.1 (GND), IC2.3 (+IN), IC2.5 (+IN), IC3.4 (I3), IC3.7 (VEE), IC3.8 (GND), INPUTS1.4, POTS.17, R22.2, R23.1, R24.2, V1.8 (-UB)
unnamed: CD4017.9 (Q8), CD4017.15 (RES), R22.1, RESET_AFTER_2.1, RESET_AFTER_4.1, RESET_BUTTON.2
unnamed: 1K3.1, C4.2
unnamed: CD4017.3 (Q0), POTS.1
unnamed: CD4017.2 (Q1), POTS.3
unnamed: CD4017.4 (Q2), POTS.5, RESET_AFTER_2.2
unnamed: CD4017.7 (Q3), POTS.7
unnamed: CD4017.10 (Q4), POTS.9
unnamed: CD4017.1 (Q5), POTS.11, RESET_AFTER_4.2
unnamed: CD4017.5 (Q6), POTS.13
unnamed: CD4017.6 (Q7), POTS.15
unnamed: POTS.2, R3.2
unnamed: POTS.4, R9.2
unnamed: POTS.6, R8.2
unnamed: POTS.8, R7.2
unnamed: POTS.10, R6.2
unnamed: POTS.12, R5.2
unnamed: POTS.14, R4.2
unnamed: POTS.16, R2.2
unnamed: IC2.2 (-IN), R2.1, R3.1, R4.1, R5.1, R6.1, R7.1, R8.1, R9.1, R10.1
unnamed: IC2.1 (OUT), R10.2, R12.2
unnamed: IC2.6 (-IN), R11.2, R12.1
unnamed: IC3.15 (F), R17.1
unnamed: D2.1 (10), R18.2
unnamed: D2.2 (9), R17.2
unnamed: D2.4 (1), R16.2
unnamed: D2.5 (2), R15.2
unnamed: D2.7 (4), R14.2
unnamed: D2.9 (6), R13.2
unnamed: D2.10 (7), R1.2
unnamed: LED9.K (C), R23.2
unnamed: GATE_POT.2, R21.1
unnamed: 1K3.2, 1K4.1, 2N2.C
unnamed: C4.1, D1.A, IC1.2 (TR), R20.1
unnamed: C1.1, IC1.5 (CV)
unnamed: C3.+, IC1.6 (THR), IC1.7 (DIS), R21.2
unnamed: 1K1.1, IC1.3 (Q), LED9.A
unnamed: IC3.9 (A), R1.1
unnamed: IC3.10 (B), R13.1
unnamed: IC3.11 (C), R14.1
unnamed: IC3.12 (D), R15.1
unnamed: IC3.13 (E), R16.1
unnamed: IC3.14 (G), R18.1
unnamed: 2N2.B, R19.1
Q1: IC3.5 (I0), V1.14 (QA)
Q2: IC3.3 (I1), V1.13 (QB)
Q3: IC3.2 (I2), V1.12 (QC)

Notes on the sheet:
Gate control. From 160ms to 1.8s using a 10k pot

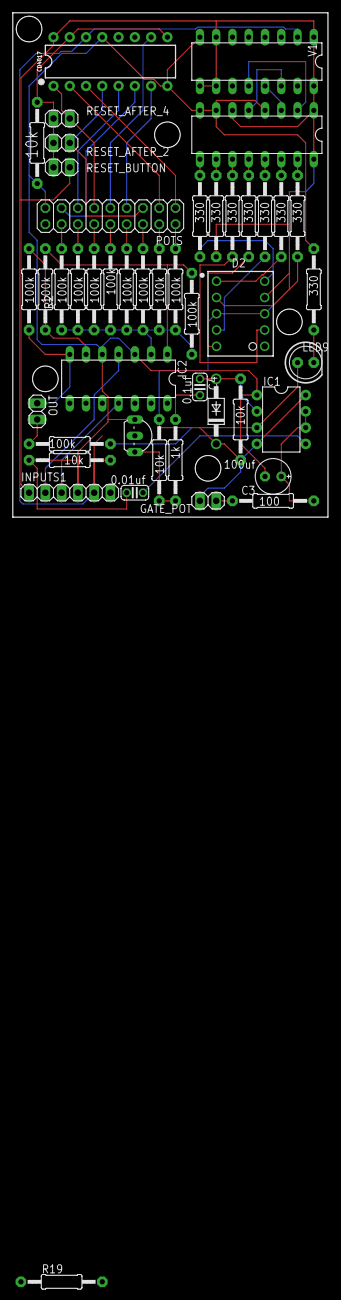
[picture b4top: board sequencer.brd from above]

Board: 2 copper layers, 49.2 x 78.7 mm, 46 parts (0 on the bottom side), 53 nets.

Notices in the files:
parts and their libraries:
SparkFun-IC-Microcontroller: Licensing: Creative Commons ShareAlike 4.0 International - https://creativecommons.org/licenses/by-sa/4.0
Wurth_7 Segments Display_WL-T7DS: Copyright: Würth Elektronik
